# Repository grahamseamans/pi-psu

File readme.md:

# THE PINS ON BOTH TRANSISTORS ARE FLIPPED FOR BASE AND COLLECTOR. otherwise it works.

# Pi PSU

A **5V linear power supply** designed for Raspberry Pi and similar devices.

## Overview

This project provides a stable 5V output for powering Raspberry Pi boards and other low-power electronics with out using switching supplies.

## PCB Design

Below is a render of the PCB layout:

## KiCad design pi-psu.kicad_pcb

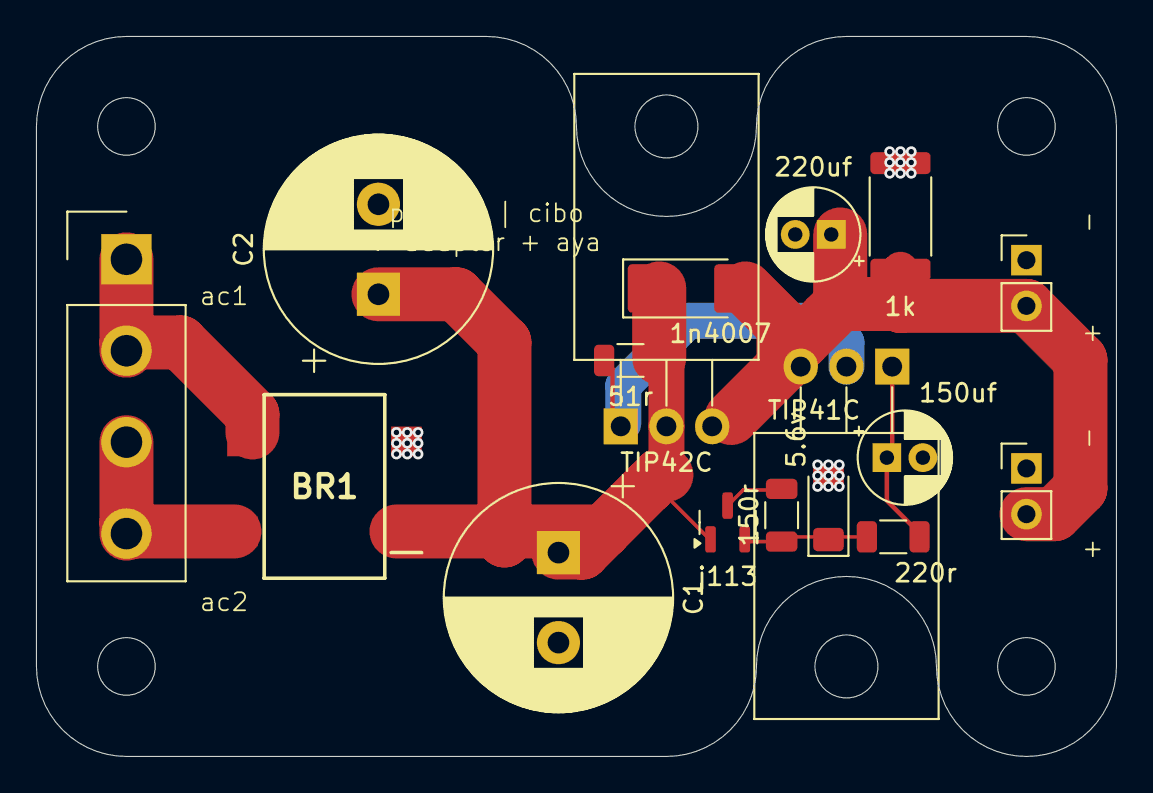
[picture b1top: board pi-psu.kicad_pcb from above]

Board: 2 copper layers, 60.0 x 40.0 mm, 21 parts (0 on the bottom side), 9 nets.

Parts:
BR1: RTT410; SOP500P990X180-4N
C1, C2: 4700uf; CP_Radial_D12.5mm_P5.00mm
C3: 150uf; CP_Radial_D5.0mm_P2.00mm
C4: 220uf; CP_Radial_D5.0mm_P2.00mm
D5: 5.6v; D_MiniMELF
D6: 1n4007; D_MELF
H1, H2, H3, H4: MountingHole; MountingHole_3.2mm_M3_ISO7380
P1, P2: Conn_02x01; PinHeader_1x02_P2.54mm_Vertical
P3: Conn_01x04_Pin; Samtec_HPM-04-01-x-S_Straight_1x04_Pitch5.08mm
Q1: j113; SOT-23
Q3: TIP42C; TO-220-3_Horizontal_TabDown
Q4: TIP41C; TO-220-3_Horizontal_TabDown
R1: 150r; R_1206_3216Metric
R2: 220r; R_1206_3216Metric
R3: 51r; R_1206_3216Metric
R4: 1k; R_2512_6332Metric

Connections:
0: C1.2, C2.2, C3.2, C4.2, D5.2 (A), P1.1, P2.1, R4.2
unnamed: BR1.3 (~_1), P3.1, P3.2
unnamed: Q1.3 (G), R1.1
unnamed: Q3.1 (B), Q4.2 (C), R3.2
ac: BR1.4 (~_2), P3.3, P3.4
out: C4.1, D6.2 (A), P1.2, P2.2, Q3.2 (C), Q4.3 (E), R4.1
pre-reg: BR1.1 (+), C1.1, C2.1, D6.1 (K), Q1.1 (D), Q3.3 (E), R3.1
vref: C3.1, Q4.1 (B), R2.2
zener-in: D5.1 (K), Q1.2 (S), R1.2, R2.1

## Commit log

2024-12-25 small clean
2024-12-25 moved active
2024-12-25 cleaned up front silk screen
2024-12-25 readme
2024-12-25 made power traces 4mm
2024-12-25 removed lock files from git
2025-07-20 doenst work with tip41 and 41
2025-07-20 sims well, sending to jlc
